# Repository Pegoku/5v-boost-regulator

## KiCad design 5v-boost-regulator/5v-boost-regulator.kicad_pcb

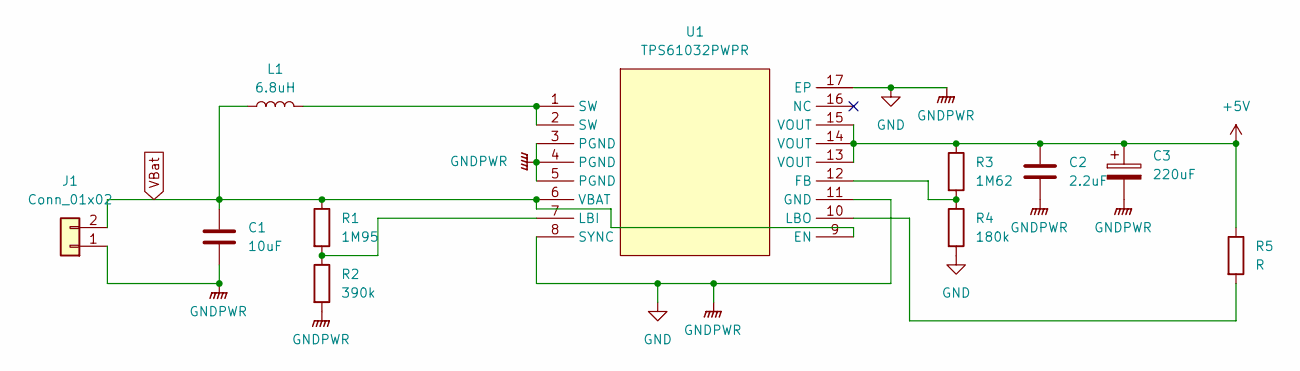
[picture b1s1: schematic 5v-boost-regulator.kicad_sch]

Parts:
C1: 10uF; C_1206_3216Metric
C2: 2.2uF; C_1206_3216Metric
C3: 220uF; CP_Elec_6.3x7.7; LCSC C2887273
J1: Conn_01x02; PinHeader_1x02_P2.54mm_Horizontal
L1: 6.8uH; L_Sunlord_MWSA1004S; LCSC C2921230
R1: 1M95; R_1206_3216Metric
R2: 390k; R_1206_3216Metric
R3: 1M62; R_1206_3216Metric
R4: 180k; R_1206_3216Metric
R5: R; R_1206_3216Metric
U1: TPS61032PWPR; HTSSOP-16_L5.0-W4.4-P0.65-LS6.4-BL-EP; LCSC Part C88716

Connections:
+5V: C2.1, C3.1, R3.1, R5.1, U1.13 (VOUT), U1.14 (VOUT), U1.15 (VOUT); also elsewhere on the board
GND: C1.2, C2.2, C3.2, J1.1, R2.2, R4.2, U1.3 (PGND), U1.4 (PGND), U1.5 (PGND), U1.8 (SYNC), U1.11 (GND), U1.17 (EP)
unnamed 2: R5.2, U1.10 (LBO); also elsewhere on the board
unnamed: L1.1, U1.1 (SW), U1.2 (SW)
unnamed: R3.2, R4.1, U1.12 (FB)
unnamed: R1.2, R2.1, U1.7 (LBI)
VBat: C1.1, J1.2, L1.2, R1.1, U1.6 (VBAT), U1.9 (EN)

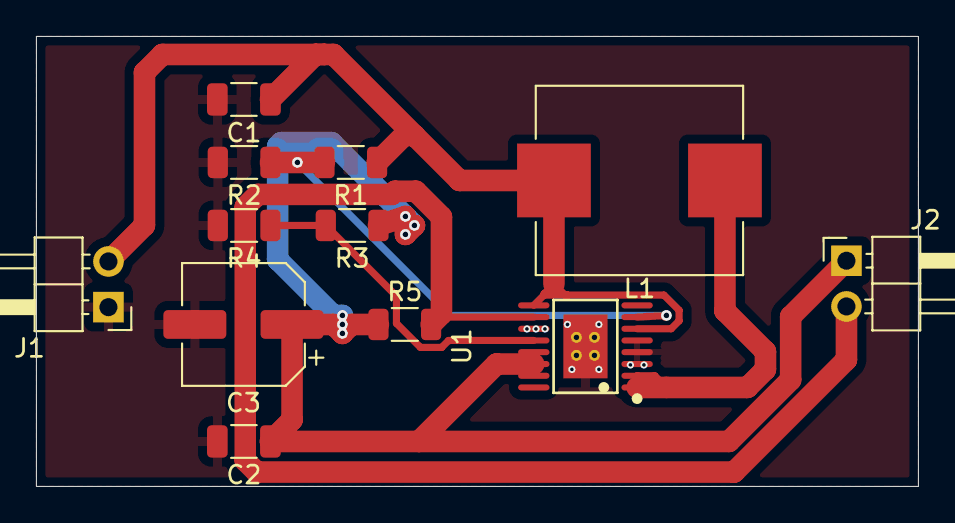
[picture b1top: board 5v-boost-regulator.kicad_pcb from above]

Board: 2 copper layers, 49.0 x 25.0 mm, 12 parts (0 on the bottom side), 7 nets.

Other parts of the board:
J2: Conn_01x02; PinHeader_1x02_P2.54mm_Horizontal

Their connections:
+5V: J2.1; also elsewhere on the board
unnamed 2: J2.2; also elsewhere on the board

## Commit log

2024-08-30 start
2024-08-30 finish
2024-08-31 Rename 5v-boost-regulator/5v-boost-regulator-backups/Screenshot.png to 5v-boost-regulator/Screenshot.png
